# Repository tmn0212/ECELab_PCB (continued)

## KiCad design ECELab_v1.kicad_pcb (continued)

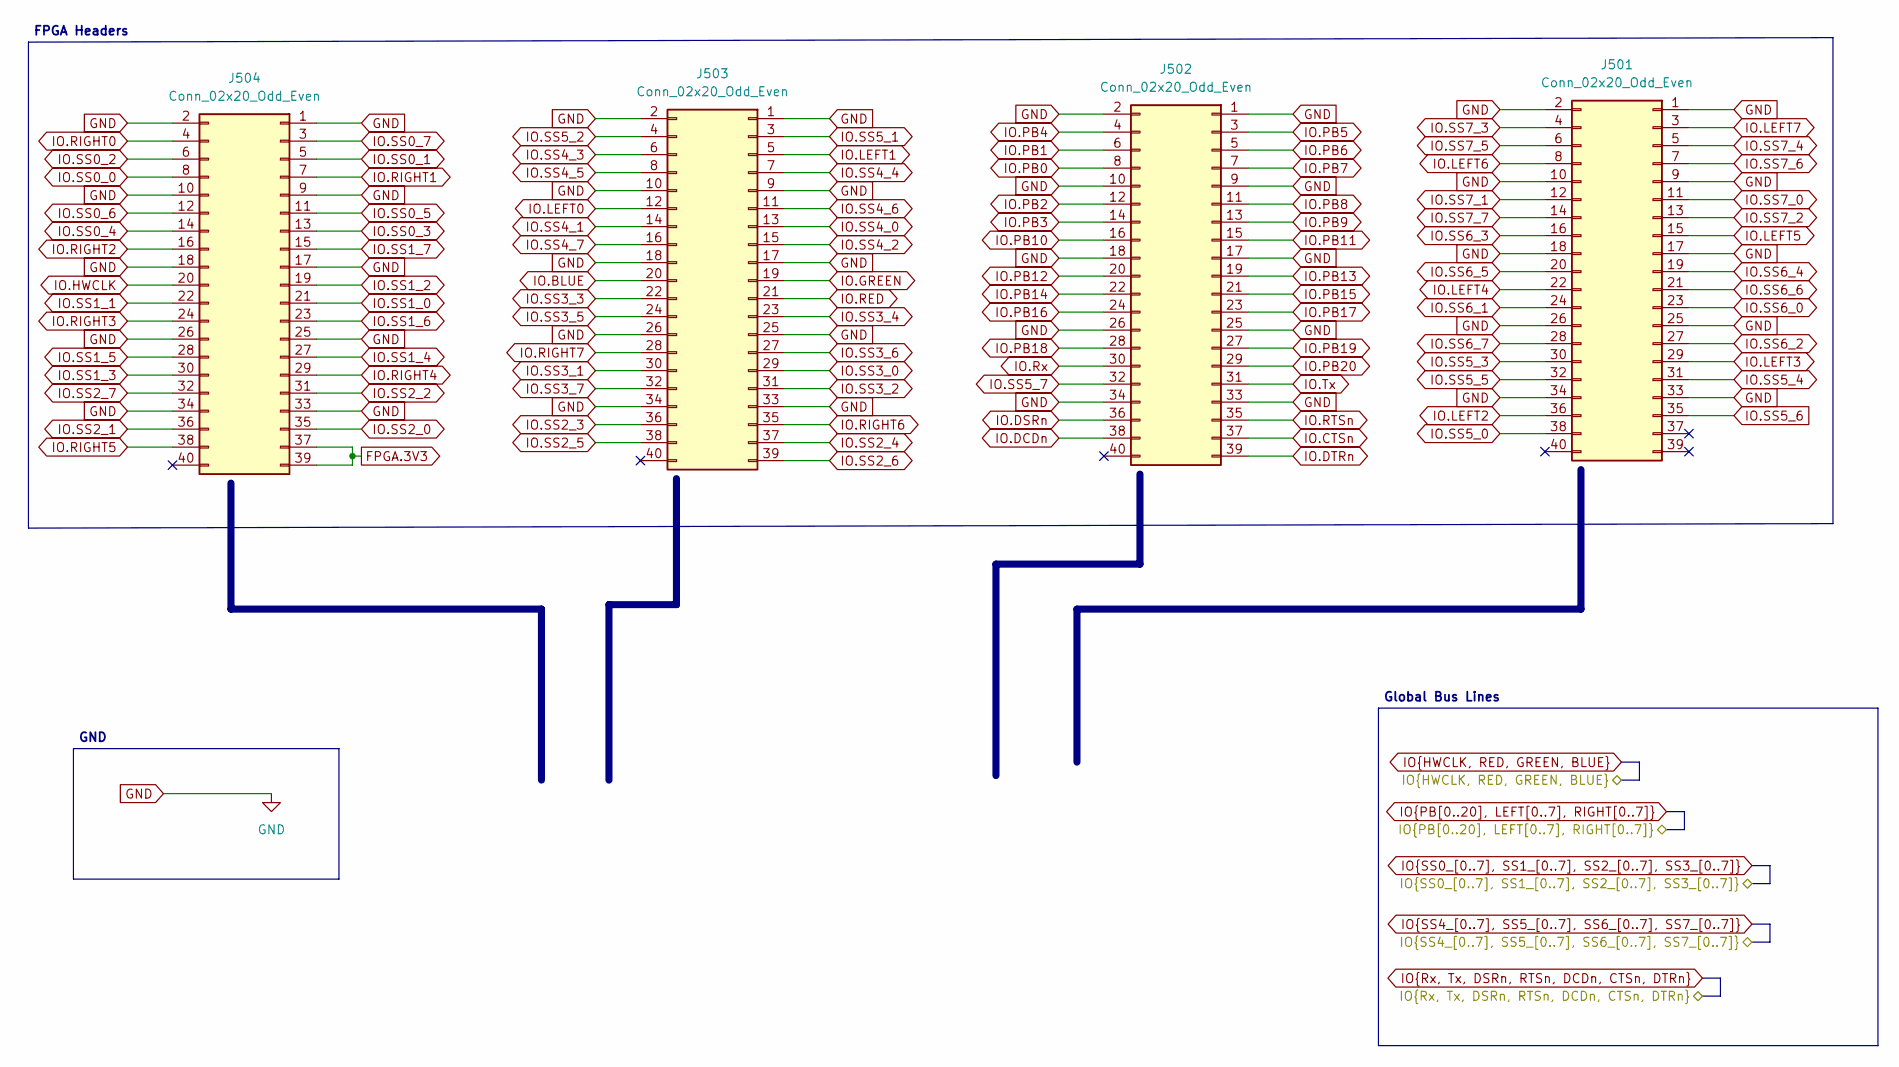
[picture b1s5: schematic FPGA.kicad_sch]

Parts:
J501, J502, J503, J504: Conn_02x20_Odd_Even; PinHeader_2x20_P2.54mm_Vertical; LCSC C5224014

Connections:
/GPIO Expansion/IO.SS4_0: J503.13; also elsewhere on the board
/GPIO Expansion/IO.SS4_1: J503.14; also elsewhere on the board
/GPIO Expansion/IO.SS4_2: J503.15; also elsewhere on the board
/GPIO Expansion/IO.SS4_3: J503.6; also elsewhere on the board
/GPIO Expansion/IO.SS4_4: J503.7; also elsewhere on the board
/GPIO Expansion/IO.SS4_5: J503.8; also elsewhere on the board
/GPIO Expansion/IO.SS4_6: J503.11; also elsewhere on the board
/GPIO Expansion/IO.SS4_7: J503.16; also elsewhere on the board
/GPIO Expansion/IO.SS5_0: J501.38; also elsewhere on the board
/GPIO Expansion/IO.SS5_1: J503.3; also elsewhere on the board
/GPIO Expansion/IO.SS5_2: J503.4; also elsewhere on the board
/GPIO Expansion/IO.SS5_3: J501.30; also elsewhere on the board
/GPIO Expansion/IO.SS5_4: J501.31; also elsewhere on the board
/GPIO Expansion/IO.SS5_5: J501.32; also elsewhere on the board
/GPIO Expansion/IO.SS5_6: J501.35; also elsewhere on the board
/GPIO Expansion/IO.SS5_7: J502.32; also elsewhere on the board
/GPIO Expansion/IO.SS6_0: J501.23; also elsewhere on the board
/GPIO Expansion/IO.SS6_1: J501.24; also elsewhere on the board
/GPIO Expansion/IO.SS6_2: J501.27; also elsewhere on the board
/GPIO Expansion/IO.SS6_3: J501.16; also elsewhere on the board
/GPIO Expansion/IO.SS6_4: J501.19; also elsewhere on the board
/GPIO Expansion/IO.SS6_5: J501.20; also elsewhere on the board
/GPIO Expansion/IO.SS6_6: J501.21; also elsewhere on the board
/GPIO Expansion/IO.SS6_7: J501.28; also elsewhere on the board
/GPIO Expansion/IO.SS7_0: J501.11; also elsewhere on the board
/GPIO Expansion/IO.SS7_1: J501.12; also elsewhere on the board
/GPIO Expansion/IO.SS7_2: J501.13; also elsewhere on the board
/GPIO Expansion/IO.SS7_3: J501.4; also elsewhere on the board
/GPIO Expansion/IO.SS7_4: J501.5; also elsewhere on the board
/GPIO Expansion/IO.SS7_5: J501.6; also elsewhere on the board
/GPIO Expansion/IO.SS7_6: J501.7; also elsewhere on the board
/GPIO Expansion/IO.SS7_7: J501.14; also elsewhere on the board
FPGA.3V3: J504.37, J504.39; also elsewhere on the board
GND: J501.1, J501.2, J501.9, J501.10, J501.17, J501.18, J501.25, J501.26, J501.33, J501.34, J502.1, J502.2, J502.9, J502.10, J502.17, J502.18, J502.25, J502.26, J502.33, J502.34, J503.1, J503.2, J503.9, J503.10, J503.17, J503.18, J503.25, J503.26, J503.33, J503.34, J504.1, J504.2, J504.9, J504.10, J504.17, J504.18, J504.25, J504.26, J504.33, J504.34; also elsewhere on the board
IO.BLUE: J503.20; also elsewhere on the board
IO.CTSn: J502.37; also elsewhere on the board
IO.DCDn: J502.38; also elsewhere on the board
IO.DSRn: J502.36; also elsewhere on the board
IO.DTRn: J502.39; also elsewhere on the board
IO.GREEN: J503.19; also elsewhere on the board
IO.HWCLK: J504.20; also elsewhere on the board
IO.LEFT0: J503.12; also elsewhere on the board
IO.LEFT1: J503.5; also elsewhere on the board
IO.LEFT2: J501.36; also elsewhere on the board
IO.LEFT3: J501.29; also elsewhere on the board
IO.LEFT4: J501.22; also elsewhere on the board
IO.LEFT5: J501.15; also elsewhere on the board
IO.LEFT6: J501.8; also elsewhere on the board
IO.LEFT7: J501.3; also elsewhere on the board
IO.PB0: J502.8; also elsewhere on the board
IO.PB1: J502.6; also elsewhere on the board
IO.PB2: J502.12; also elsewhere on the board
IO.PB3: J502.14; also elsewhere on the board
IO.PB4: J502.4; also elsewhere on the board
IO.PB5: J502.3; also elsewhere on the board
IO.PB6: J502.5; also elsewhere on the board
IO.PB7: J502.7; also elsewhere on the board
IO.PB8: J502.11; also elsewhere on the board
IO.PB9: J502.13; also elsewhere on the board
IO.PB10: J502.16; also elsewhere on the board
IO.PB11: J502.15; also elsewhere on the board
IO.PB12: J502.20; also elsewhere on the board
IO.PB13: J502.19; also elsewhere on the board
IO.PB14: J502.22; also elsewhere on the board
IO.PB15: J502.21; also elsewhere on the board
IO.PB16: J502.24; also elsewhere on the board
IO.PB17: J502.23; also elsewhere on the board
IO.PB18: J502.28; also elsewhere on the board
IO.PB19: J502.27; also elsewhere on the board
IO.PB20: J502.29; also elsewhere on the board
IO.RED: J503.21; also elsewhere on the board
IO.RIGHT0: J504.4; also elsewhere on the board
IO.RIGHT1: J504.7; also elsewhere on the board
IO.RIGHT2: J504.16; also elsewhere on the board
IO.RIGHT3: J504.24; also elsewhere on the board
IO.RIGHT4: J504.29; also elsewhere on the board
IO.RIGHT5: J504.38; also elsewhere on the board
IO.RIGHT6: J503.35; also elsewhere on the board
IO.RIGHT7: J503.28; also elsewhere on the board
IO.RTSn: J502.35; also elsewhere on the board
IO.Rx: J502.30; also elsewhere on the board
IO.SS0_0: J504.8; also elsewhere on the board
IO.SS0_1: J504.5; also elsewhere on the board
IO.SS0_2: J504.6; also elsewhere on the board
IO.SS0_3: J504.13; also elsewhere on the board
IO.SS0_4: J504.14; also elsewhere on the board
IO.SS0_5: J504.11; also elsewhere on the board
IO.SS0_6: J504.12; also elsewhere on the board
IO.SS0_7: J504.3; also elsewhere on the board
IO.SS1_0: J504.21; also elsewhere on the board
IO.SS1_1: J504.22; also elsewhere on the board
IO.SS1_2: J504.19; also elsewhere on the board
IO.SS1_3: J504.30; also elsewhere on the board
IO.SS1_4: J504.27; also elsewhere on the board
IO.SS1_5: J504.28; also elsewhere on the board
IO.SS1_6: J504.23; also elsewhere on the board
IO.SS1_7: J504.15; also elsewhere on the board
IO.SS2_0: J504.35; also elsewhere on the board
IO.SS2_1: J504.36; also elsewhere on the board
IO.SS2_2: J504.31; also elsewhere on the board
IO.SS2_3: J503.36; also elsewhere on the board
IO.SS2_4: J503.37; also elsewhere on the board
IO.SS2_5: J503.38; also elsewhere on the board
IO.SS2_6: J503.39; also elsewhere on the board
IO.SS2_7: J504.32; also elsewhere on the board
IO.SS3_0: J503.29; also elsewhere on the board
IO.SS3_1: J503.30; also elsewhere on the board
IO.SS3_2: J503.31; also elsewhere on the board
IO.SS3_3: J503.22; also elsewhere on the board
IO.SS3_4: J503.23; also elsewhere on the board
IO.SS3_5: J503.24; also elsewhere on the board
IO.SS3_6: J503.27; also elsewhere on the board
IO.SS3_7: J503.32; also elsewhere on the board
IO.Tx: J502.31; also elsewhere on the board

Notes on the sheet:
Global Bus Lines
GND
FPGA Headers

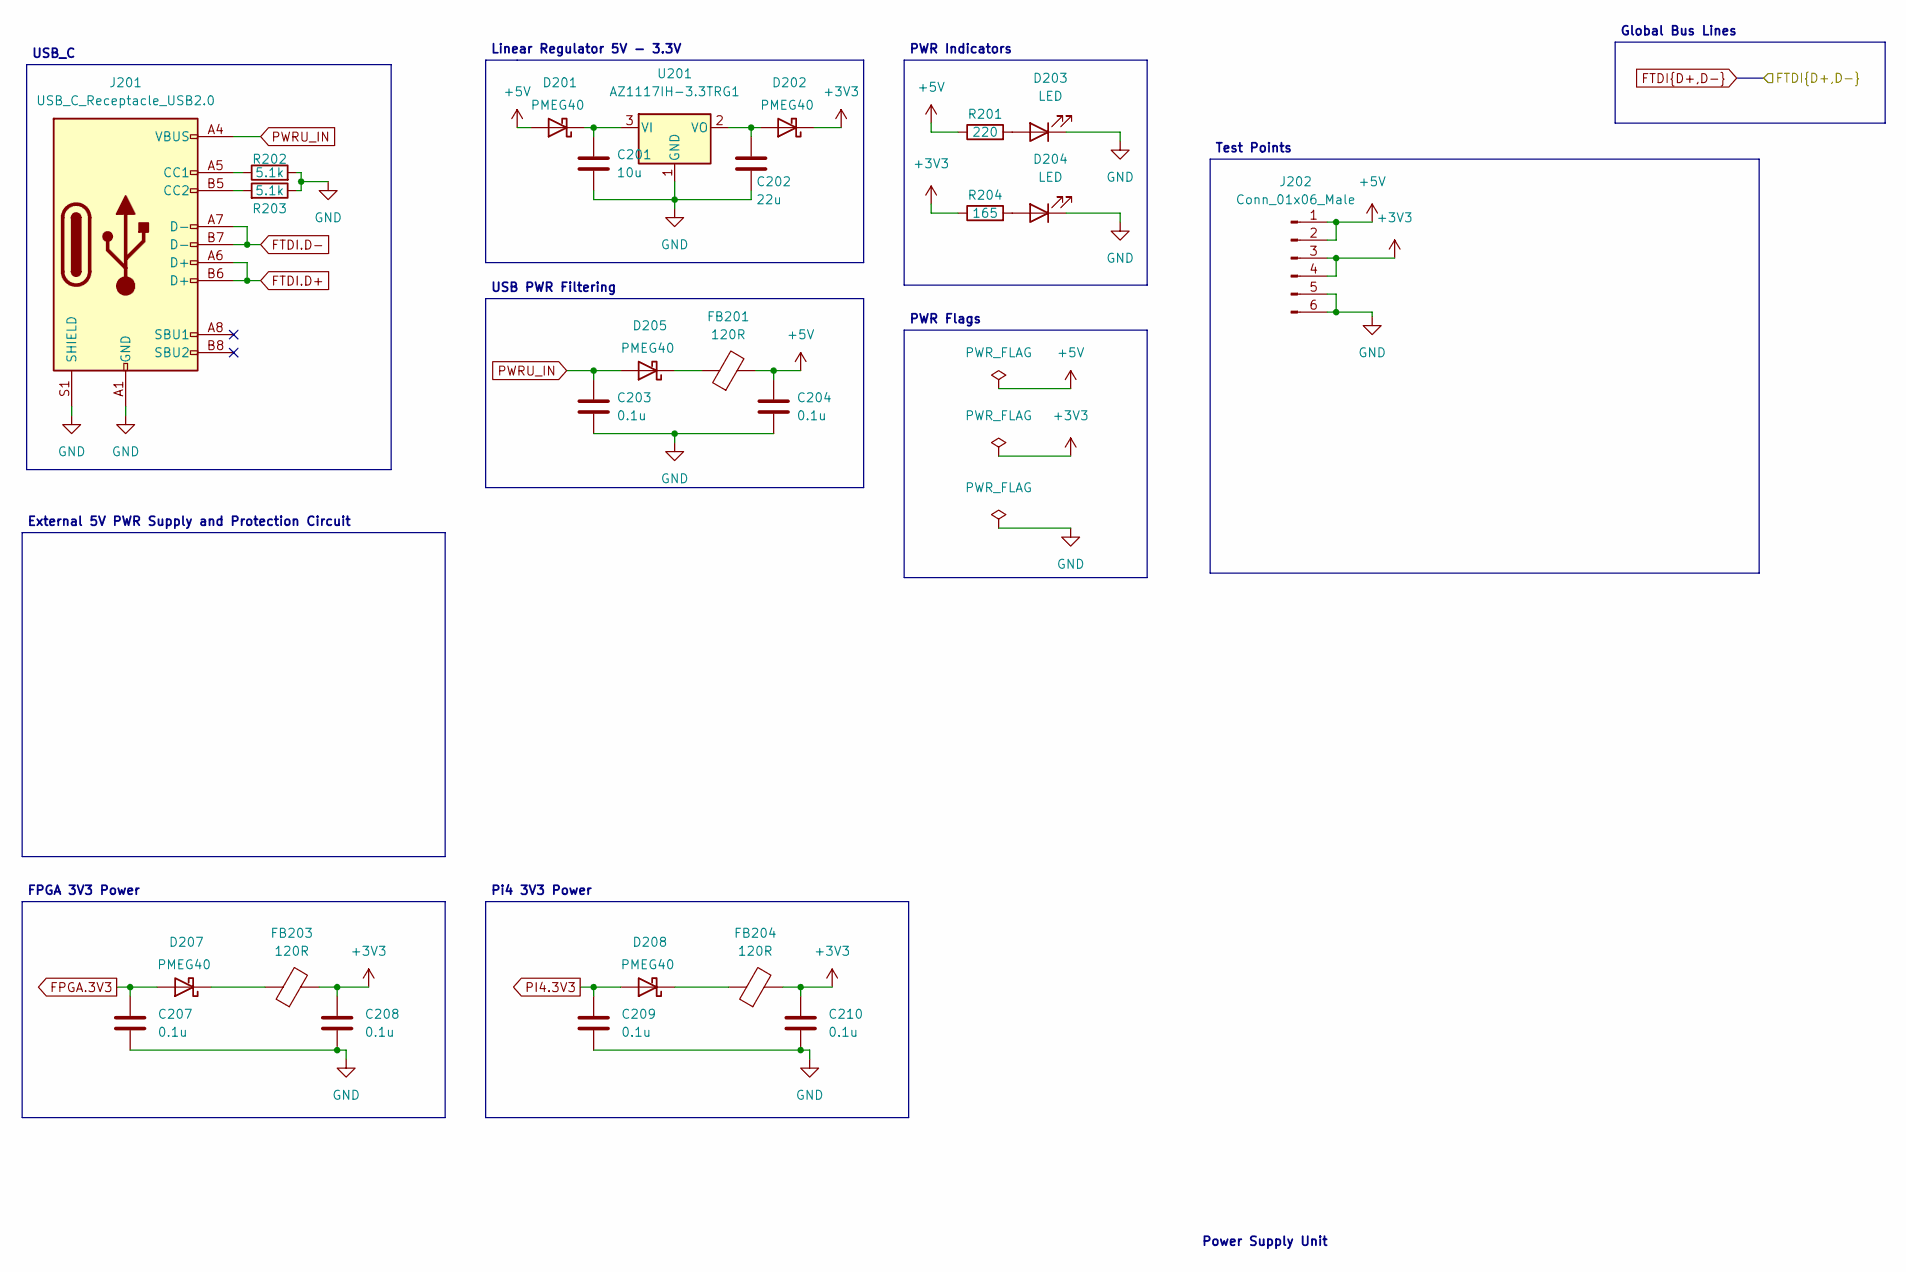
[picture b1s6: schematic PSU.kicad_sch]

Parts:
C201: 10u; C_0402_1005Metric; LCSC Part Number C76991
C202: 22u; C_0402_1005Metric; LCSC Part Number C907955
C203, C204, C207, C208, C209, C210: 0.1u; C_0402_1005Metric; LCSC Part Number C1525
D201, D202, D205, D207, D208: PMEG40; D_SOD-323; LCSC Part Number C36975
D203: LED; LED_0402_1005Metric; LCSC Part Number C136765
D204: LED; LED_0402_1005Metric; LCSC Part Number C165977
FB201, FB203, FB204: 120R; L_0603_1608Metric; LCSC Part Number C279682
J201: USB_C_Receptacle_USB2.0; USB_C_Receptacle_HRO_TYPE-C-31-M-12; LCSC Part Number C165948
J202: Conn_01x06_Male; PinHeader_1x06_P2.54mm_Vertical
R201: 220; R_0402_1005Metric; LCSC Part Number C25091
R202, R203: 5.1k; R_0402_1005Metric; LCSC Part Number C105872
R204: 165; R_0402_1005Metric; LCSC Part Number C159101
U201: AZ1117IH-3.3TRG1; SOT-223-3_TabPin2; LCSC Part Number C108495

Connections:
+5V: C204.1, D201.2 (A), FB201.2, J202.1, J202.2, R201.1; also elsewhere on the board
FPGA.3V3: C207.1, D207.2 (A); also elsewhere on the board
FTDI.D+: J201.A6 (D+), J201.B6 (D+); also elsewhere on the board
FTDI.D-: J201.A7 (D-), J201.B7 (D-); also elsewhere on the board
GND: C201.2, C202.2, C203.2, C204.2, C207.2, C208.2, C209.2, C210.2, D203.1 (K), D204.1 (K), J201.A1 (GND), J201.A12 (GND), J201.B1 (GND), J201.B12 (GND), J201.S1 (SHIELD), J202.5, J202.6, R202.2, R203.1, U201.1 (GND); also elsewhere on the board
unnamed: C201.1, D201.1 (K), U201.3 (VI)
unnamed: C202.1, D202.2 (A), U201.2 (VO)
unnamed: D203.2 (A), R201.2
unnamed: D204.2 (A), R204.2
unnamed: D205.1 (K), FB201.1
unnamed: D207.1 (K), FB203.1
unnamed: D208.1 (K), FB204.1
unnamed: J201.A5 (CC1), R202.1
unnamed: J201.B5 (CC2), R203.2
PI4.3V3: C209.1, D208.2 (A); also elsewhere on the board
PWRU_IN: C203.1, D205.2 (A), J201.A4 (VBUS), J201.A9 (VBUS), J201.B4 (VBUS), J201.B9 (VBUS)

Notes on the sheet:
Test Points
FPGA 3V3 Power
USB PWR Filtering
Global Bus Lines
USB_C
Linear Regulator 5V - 3.3V
PWR Indicators
External 5V PWR Supply and Protection Circuit
Pi4 3V3 Power
Power Supply Unit
PWR Flags

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
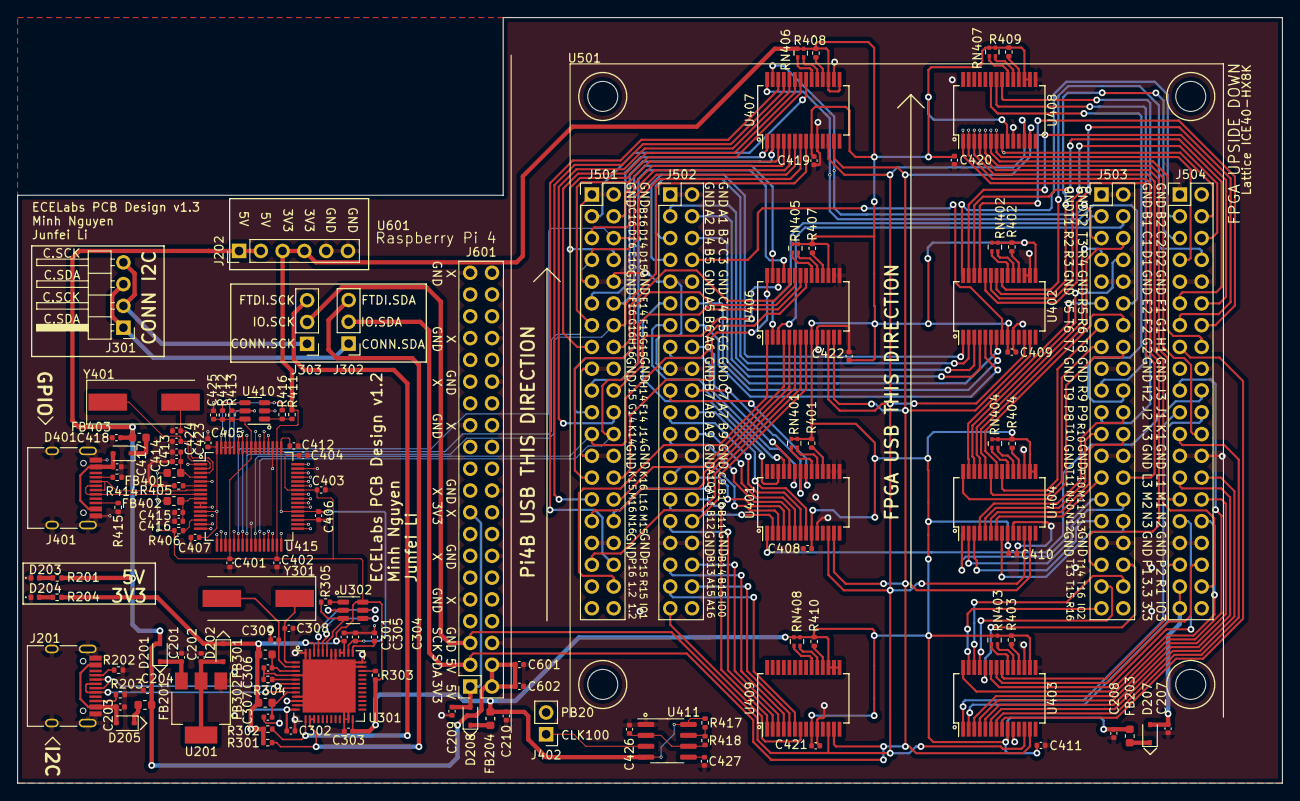
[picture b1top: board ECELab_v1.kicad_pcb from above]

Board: 4 copper layers, 147.5 x 89.3 mm, 127 parts (0 on the bottom side), 191 nets.

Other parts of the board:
U501: ICE40-HX8K_Breakout_Board; ICE40-HX8K Breakout Board
U601: RASPBERRY_PI_4B_4GB; MODULE_RASPBERRY_PI_4B_4GB

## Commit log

2023-05-16 Init Commit
2023-05-16 Update on Schematic & Footprint Update
2023-05-23 Complete Draft 1 of PCB Design
2023-05-25 Draft 1 complete
2023-05-29 Complete SPI Design
2023-05-31 Small Update
2023-06-02 Update 1
2023-07-26 Update 2nd iteration
2023-07-30 Update 7/30
2023-08-02 Update 8/2
2023-08-03 Complete Design v2
2023-08-04 Complete Design
2023-08-05 Complete manufacture v1.2
2023-08-16 Fix FTDI 1 Channel SDA issue
2023-08-17 Complete V1.3
